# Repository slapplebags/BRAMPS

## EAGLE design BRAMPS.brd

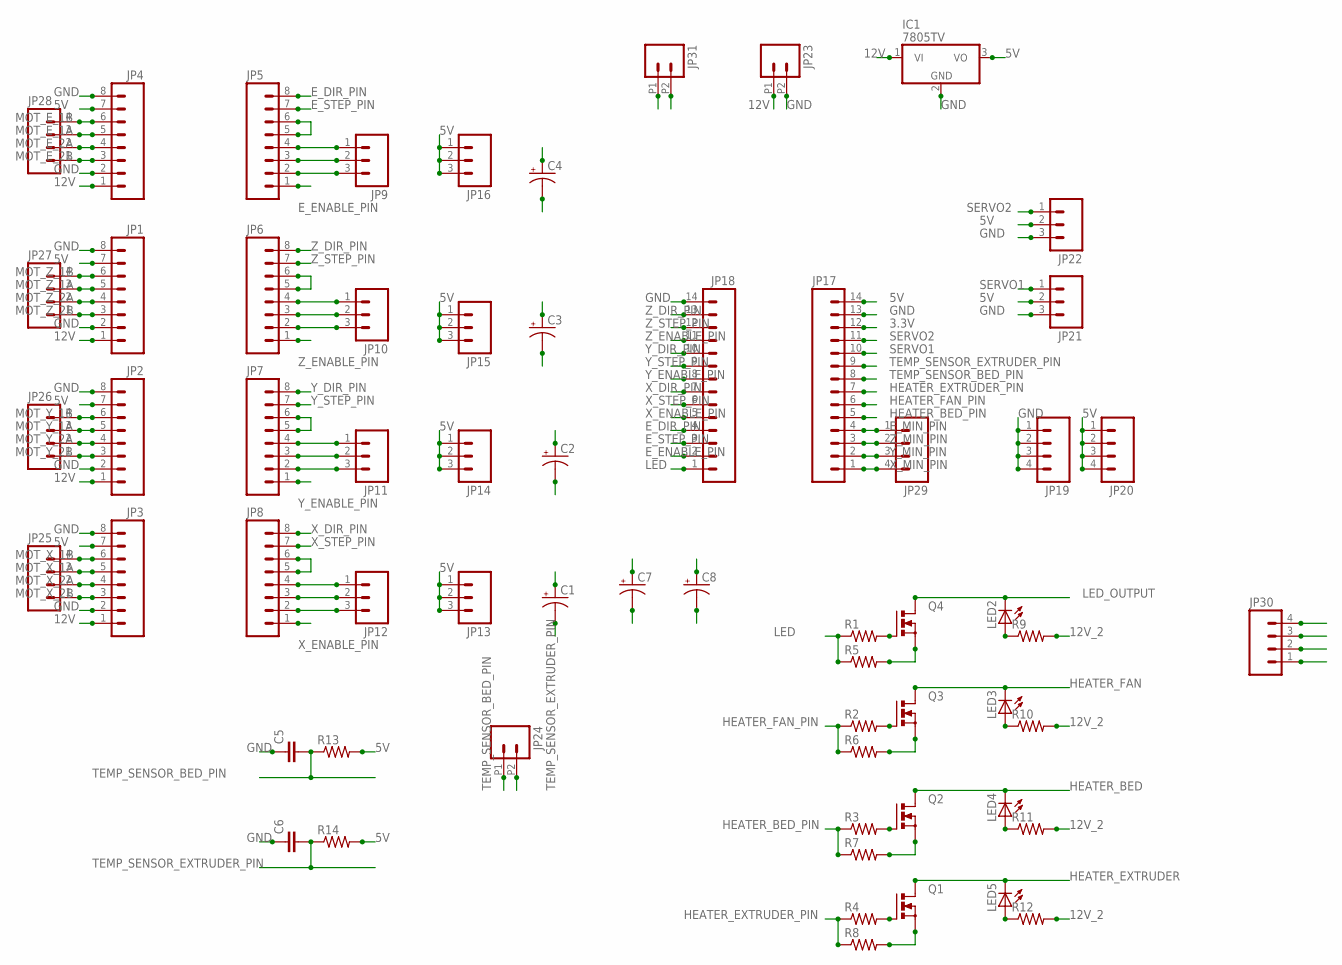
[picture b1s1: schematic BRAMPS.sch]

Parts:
C1, C2, C3, C4, C7, C8: CAP_POLPTH2; CPOL-RADIAL-10UF-25V
C5, C6: CAP0805; 0805
IC1: 7805TV; TO220V
JP1, JP2, JP3, JP4, JP5, JP6, JP7, JP8: M08NO_SILK_FEMALE_PTH; 1X08_NO_SILK
JP9, JP10, JP11, JP12, JP13, JP14, JP15, JP16, JP21, JP22: M03PTH; 1X03
JP17, JP18: M14; 1X14
JP19, JP20, JP29: M04NO_SILK_ALL_ROUND; 1X04_NO_SILK_ALL_ROUND
JP23, JP24, JP31: M022.54MM_SCREWTERM; 1X02_2.54_SCREWTERM
JP25, JP26, JP27, JP28, JP30: M04SCREW; SCREWTERMINAL-3.5MM-4
LED2, LED3, LED4, LED5: LEDCHIP-LED0805; CHIP-LED0805
Q1, Q2, Q3, Q4: PMOSFET_NTO220BV; TO220BV
R1, R2, R3, R4, R5, R6, R7, R8, R9, R10, R11, R12, R13, R14: RESISTOR0805-RES; 0805

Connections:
3.3V: JP17.12
5V: C8.1 (+), IC1.3 (VO), JP1.7, JP2.7, JP3.7, JP4.7, JP13.1, JP13.2, JP13.3, JP14.1, JP14.2, JP14.3, JP15.1, JP15.2, JP15.3, JP16.1, JP16.2, JP16.3, JP17.14, JP20.1, JP20.2, JP20.3, JP20.4, JP21.2, JP22.2, R13.2, R14.2
12V: C1.1 (+), C2.1 (+), C3.1 (+), C4.1 (+), C7.1 (+), IC1.1 (VI), JP1.1, JP2.1, JP3.1, JP4.1, JP23.P1 (1)
12V_2: JP31.P1 (1), R9.2, R10.2, R11.2, R12.2
E_DIR_PIN: JP5.8, JP18.4
E_ENABLE_PIN: JP5.1, JP18.2
E_MIN_PIN: JP17.4, JP29.1
E_STEP_PIN: JP5.7, JP18.3
GND: C1.2 (-), C2.2 (-), C3.2 (-), C4.2 (-), C5.1, C6.1, C7.2 (-), C8.2 (-), IC1.2 (GND), JP1.2, JP1.8, JP2.2, JP2.8, JP3.2, JP3.8, JP4.2, JP4.8, JP17.13, JP18.14, JP19.1, JP19.2, JP19.3, JP19.4, JP21.3, JP22.3, JP23.P2 (2), Q1.S, Q2.S, Q3.S, Q4.S, R5.2, R6.2, R7.2, R8.2
GND2: JP31.P2 (2)
HEATER_BED: JP30.3, LED4.C, Q2.D
HEATER_BED_PIN: JP17.5, R3.1, R7.1
HEATER_EXTRUDER: JP30.1, LED5.C, Q1.D
HEATER_EXTRUDER_PIN: JP17.7, R4.1, R8.1
HEATER_FAN: JP30.2, LED3.C, Q3.D
HEATER_FAN_PIN: JP17.6, R2.1, R6.1
LED: JP18.1, R1.1, R5.1
LED_OUTPUT: JP30.4, LED2.C, Q4.D
MOT_E_1A: JP4.5, JP28.3
MOT_E_1B: JP4.6, JP28.4
MOT_E_2A: JP4.4, JP28.2
MOT_E_2B: JP4.3, JP28.1
MOT_X_1A: JP3.5, JP25.3
MOT_X_1B: JP3.6, JP25.4
MOT_X_2A: JP3.4, JP25.2
MOT_X_2B: JP3.3, JP25.1
MOT_Y_1A: JP2.5, JP26.3
MOT_Y_1B: JP2.6, JP26.4
MOT_Y_2A: JP2.4, JP26.2
MOT_Y_2B: JP2.3, JP26.1
MOT_Z_1A: JP1.5, JP27.3
MOT_Z_1B: JP1.6, JP27.4
MOT_Z_2A: JP1.4, JP27.2
MOT_Z_2B: JP1.3, JP27.1
unnamed: JP6.4, JP10.1
unnamed: JP6.3, JP10.2
unnamed: JP6.2, JP10.3
unnamed: JP7.4, JP11.1
unnamed: JP7.3, JP11.2
unnamed: JP7.2, JP11.3
unnamed: JP8.4, JP12.1
unnamed: JP8.3, JP12.2
unnamed: JP8.2, JP12.3
unnamed: JP6.5, JP6.6
unnamed: JP5.5, JP5.6
unnamed: JP7.5, JP7.6
unnamed: JP5.4, JP9.1
unnamed: JP5.3, JP9.2
unnamed: JP5.2, JP9.3
unnamed: JP8.5, JP8.6
unnamed: Q2.G, R3.2
unnamed: Q3.G, R2.2
unnamed: Q4.G, R1.2
unnamed: Q1.G, R4.2
unnamed: LED2.A, R9.1
unnamed: LED3.A, R10.1
unnamed: LED4.A, R11.1
unnamed: LED5.A, R12.1
SERVO1: JP17.10, JP21.1
SERVO2: JP17.11, JP22.1
TEMP_SENSOR_BED_PIN: C5.2, JP17.8, JP24.P1 (1), R13.1
TEMP_SENSOR_EXTRUDER_PIN: C6.2, JP17.9, JP24.P2 (2), R14.1
X_DIR_PIN: JP8.8, JP18.7
X_ENABLE_PIN: JP8.1, JP18.5
X_MIN_PIN: JP17.1, JP29.4
X_STEP_PIN: JP8.7, JP18.6
Y_DIR_PIN: JP7.8, JP18.10
Y_ENABLE_PIN: JP7.1, JP18.8
Y_MIN_PIN: JP17.2, JP29.3
Y_STEP_PIN: JP7.7, JP18.9
Z_DIR_PIN: JP6.8, JP18.13
Z_ENABLE_PIN: JP6.1, JP18.11
Z_MIN_PIN: JP17.3, JP29.2
Z_STEP_PIN: JP6.7, JP18.12

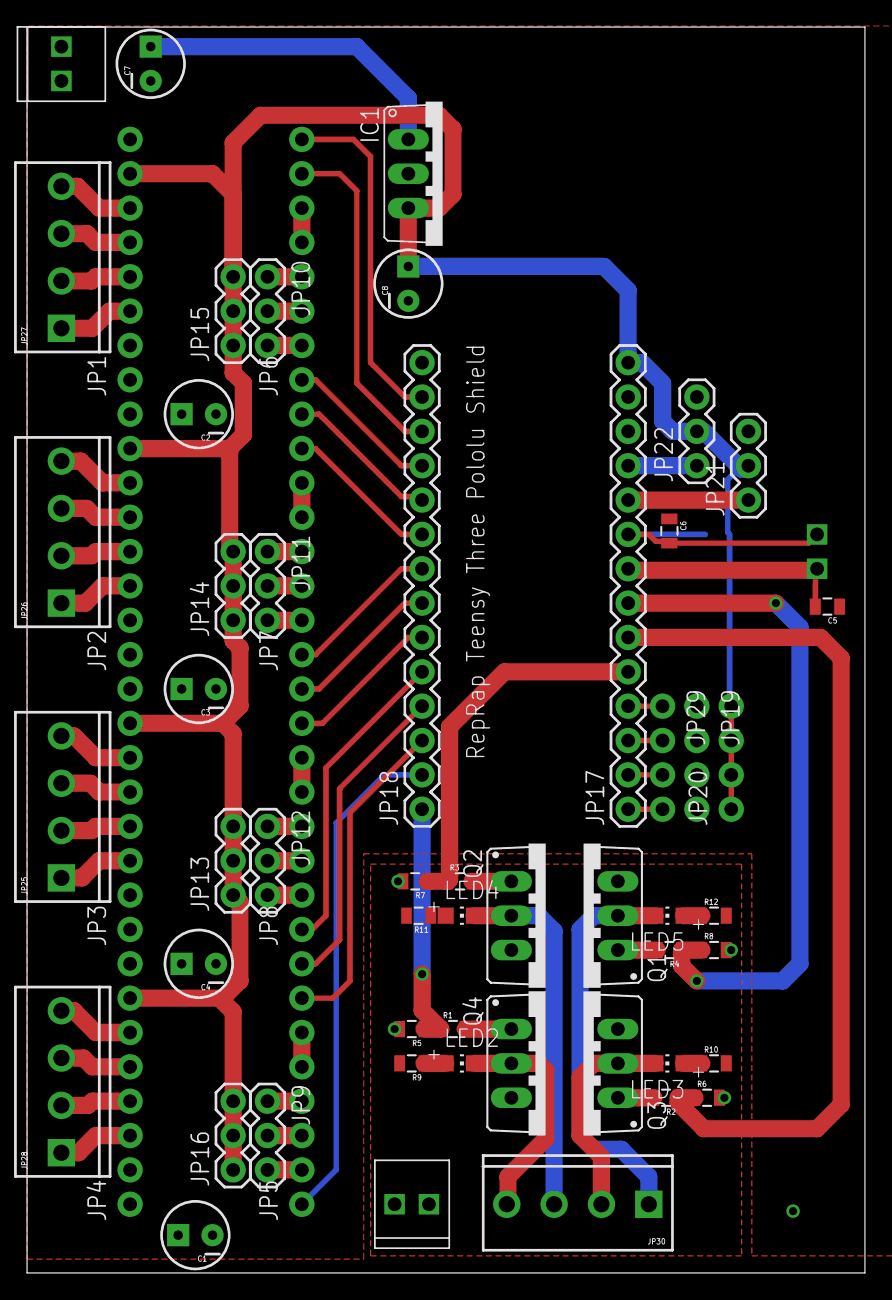
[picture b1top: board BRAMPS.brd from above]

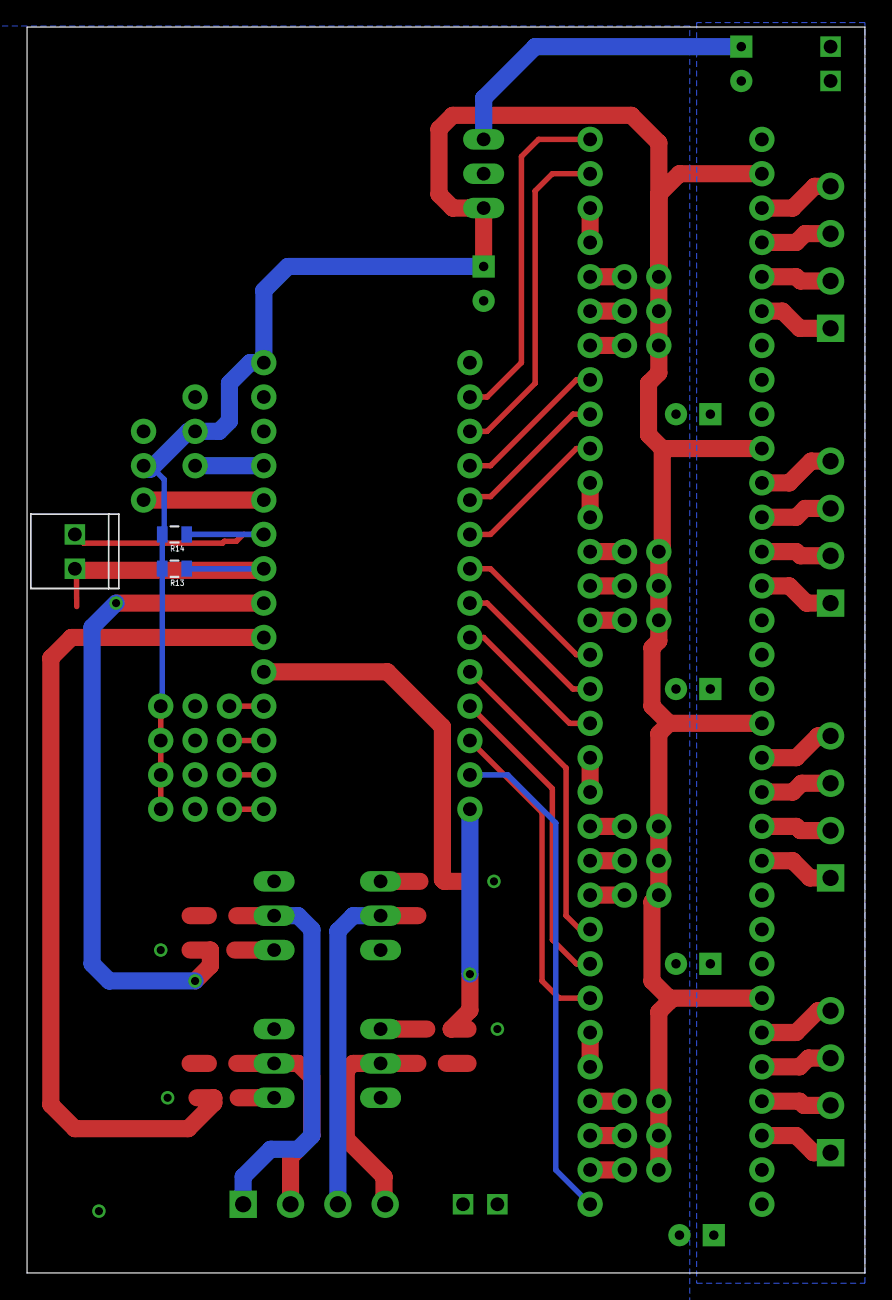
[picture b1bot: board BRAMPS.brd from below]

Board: 2 copper layers, 62.0 x 92.1 mm, 62 parts (3 on the bottom side), 72 nets.

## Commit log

2016-06-13 Initial Commit
    Copied the RAMPS schematic, replacing the Arduino board with a TEENSY3.2

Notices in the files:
parts and their libraries:
SparkFun-Connectors: Licensing: Creative Commons ShareAlike 4.0 International - https://creativecommons.org/licenses/by-sa/4.0
